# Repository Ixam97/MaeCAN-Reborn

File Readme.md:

# <b>MäCAN _Reborn_ </b>

Die zweite Generaton der MäCAN-Komponenten für den [Märklin CAN-Bus][candoku]

- <b>[MäCAN _Bootloader_][bootloader]</b><br>
    
- <b>[MäCAN _MP5x16_][mp5x16]</b><br>

- <b>[MäCAN _Dx32_][dx32]</b><br>

## Changelog

### [2022-03-26.1]
#### Hinzugefügt:
 - MP5x8+S: Kombination aus Signal- und Weichendecoder zum testen, kompatibel mit der MP5x16-Platine.
#### Änderungen:
 - MP5+D | Rückmeldefehler behoben, Einstellungen für die Schaltzeit und -verzögerung.
 - MP5x16 | Rückmeldefehler behoben.
 - Bootloader | Unterstützt nun 16-Bit Page-Addresse (Rückwärtskomatibel mit alten Updatern).
 - Bootloader | Nach einem fehlerhaften oder abgebrochenen Update wird der Programmspeicher gelöscht. Das Gerät verbleibt im Booloader, bis ein Update erfolgreich abgeschlossen wurde.
 - Allgemein | Der CAN-Ringpuffer blockiert nicht mehr, wenn er voll läuft.

### [2021-09-14.1]
#### Hinzugefügt:
- Allgemein | Source und Binarys für den maecan-updater für SRSEII und Windows.
- Bootloader | Unterstützung für NScale Grundmodule.
- MP5+D | Abwandlung des MP5x16 für die alternative Nutzung einiger Ports.
#### Änderungen:
- MP5x16 | Korrekte Abhandlung von Config-Kanal-Abfragen durch ein Userinterface.
- Bootloader | UID-Vergleich korrigiert.
### [2021-03-13.2]
#### Hinzugefügt:
- Allgemein | Fehlermeldung hinzugefügt, falls MCAN mit einem nicht unterstützten Controller verwendet wird.

### [2021-03-13.1]
#### Änderungen:
- Allgemein | Die Dokumentation in mcan.h wurde umfangreich erweitert.
- Allgemein | Die Berechnung des Hash wird durch mcan_init() übernommen. Die vorgefertigten send-Funktionen benötigen keine UID und keinen Hash mehr als Parameter. Dx32 und MP5x16 wurden entsprechend angepasst.
- Allgemein compareUID() ist jetzt Teil von MCAN.

### [2021-03-12.1]
#### Änderungen:
- Allgemein | MCAN beinhaltet nun mcp2515_basic und wurde aufgeräumt, um die Nutzung zu vereinfachen. Eine nutzung in Arduino-Sketches ist möglich.

#### Hinzugefügt:
- Dx32 | Version 1.0, Konfiguration und EEPROM-Nutzung wurde vollständig integriert. 
- Dx32 | Der DIP-Schalter stellt folgende Funktionen bereit: 1: Bootloader-Modus (noch nicht im Bootloader integriert), 2: New Line bei SLCAN zum Debugging, 3: Silent-Mode reagiert nicht auf Ping-Anfragen

### [2021-01-27.1]
#### Hinzugefügt:
- Allgemein | In mcp2515_basic ist nun SLCAN integriert. Ist das Symbol "SLCAN" definiert wird die serielle Schnittstelle als CAN-Interface genutzt. Standard sind 500000 Baud. Hierfür wurde die Interruptbehandlung in mcp2515_basic integriert. Nach `init_mcp2515()` kann mit `readCanFrame()` ausgewertet werden. SLCAN und der physische CAN werden gleichwertig behandelt. Im selben Zuge wurde für CAN-Frames ein Ring-Buffer implementiert. SLCAN ist auch im Bootloader verfügbar.

#### Änderungen:
- MP5x16 | Die Ansteuerung der Status-LED wurde an Dx32 angeglichen.

### [2021-01-25.1]
#### Hinzugefügt:
- Allgemein | Neue Funktion "sendStatus" in der mcan-Bibliothek zum senden von Statuskanalwerten.
- Dx32 | Konfigurationskanal-Werte können abgefragt werden.

### [2021-01-24.1]
#### Änderungen:
- Allgemein | Ein Fehler in der Übertragung von Konfigurationskanälen in der mcan.c wurde behoben.
- Dx32 | Basisfunktionalität wurde hergestellt (Belegterkennung mit Timeout und Gleisspannungserkennung).

### [2021-01-05.1]
#### Änderungen:
- Allgemein | Die Firmware aller Koponenten sowie des Bootloaders wurden in einer Atmel Studio-Solution zusammen geführt, um auf gemeinsame Dateien zugreifen zu können.
- Allgemein | Vereinheitlichung von Ordner- und Dateinamen ohne Umlaute.
- Allgemein | Nicht benötigte defines in mcan.h entfernt und für den ATmega1280 hinzugefügt.
- MP5x16 | Die Heartbeat-LED hat einen Fade-Effekt erhalten.
- Bootloader | Unterstützung für den Dx32 mit ATmega1280.
- Dx32 | Leitungsbenennung für zwei Rückmelde-LEDs an die Portbenennung angepasst.

#### Hinzugefügt:
- Dx32 | Erste Testsoftware mit einem Lauflicht und Helligkeitssteuerung für die Rückmelde-LEDs.

### [2020-12-26.2]
#### Änderungen:
- Bootloader + MP5x16 | Anpassung an die Compiler-Flags für die CPU-Frequenz, da Delays nicht richtig funktioniert haben.
- MP5x16 | Kleinere Änderungen, mit denen bisherige Compiler-Warnungen behandelt wurden.

### [2020-12-26.1]
#### Änderungen:
- Dx32 | Fehlerhafte Anbindung der externen Taktquelle für die USB-Schnittstelle korrigiert (Hardware V1.1).
- Bootloader | Makefile hinzugefügt, mit der der Bootloader Außerhalb von Atmel Studio für eines oder alle Boards kompilliert werden kann (Software V1.2).
- Bootloader | main.c durch maecan-bootloader.c ersetzt.

#### Hinzugefügt:
- Bootloader | Vorkompillierte Hex-Dateien für Busankoppler und MP5x16 hinzugefügt.

### [2020-12-22.1]
#### Änderungen:
- MP5x16 | Möglichkeit einer einstellbaren ID über den DIP-Schalter für eine einfachere Adressierung.

#### Hinzugefügt
- Dx32 | Erster Upload der Hardware.

### [2020-08-27.2]
#### Änderungen:
- Readme-Dateien angepasst

### [2020-08-27.1]
#### Hinzugefügt:
- MP5x16 | Erster Upload
- Bootloader |  Erster Upload

[candoku]: https://www.maerklin.de/fileadmin/media/service/software-updates/cs2CAN-Protokoll-2_0.pdf
[bootloader]: Bootloader
[mp5x16]: MäCAN_MP5x16
[dx32]: MäCAN_Dx32

[//]: # (Orange: #FE7D37, Blau: #007EC6)

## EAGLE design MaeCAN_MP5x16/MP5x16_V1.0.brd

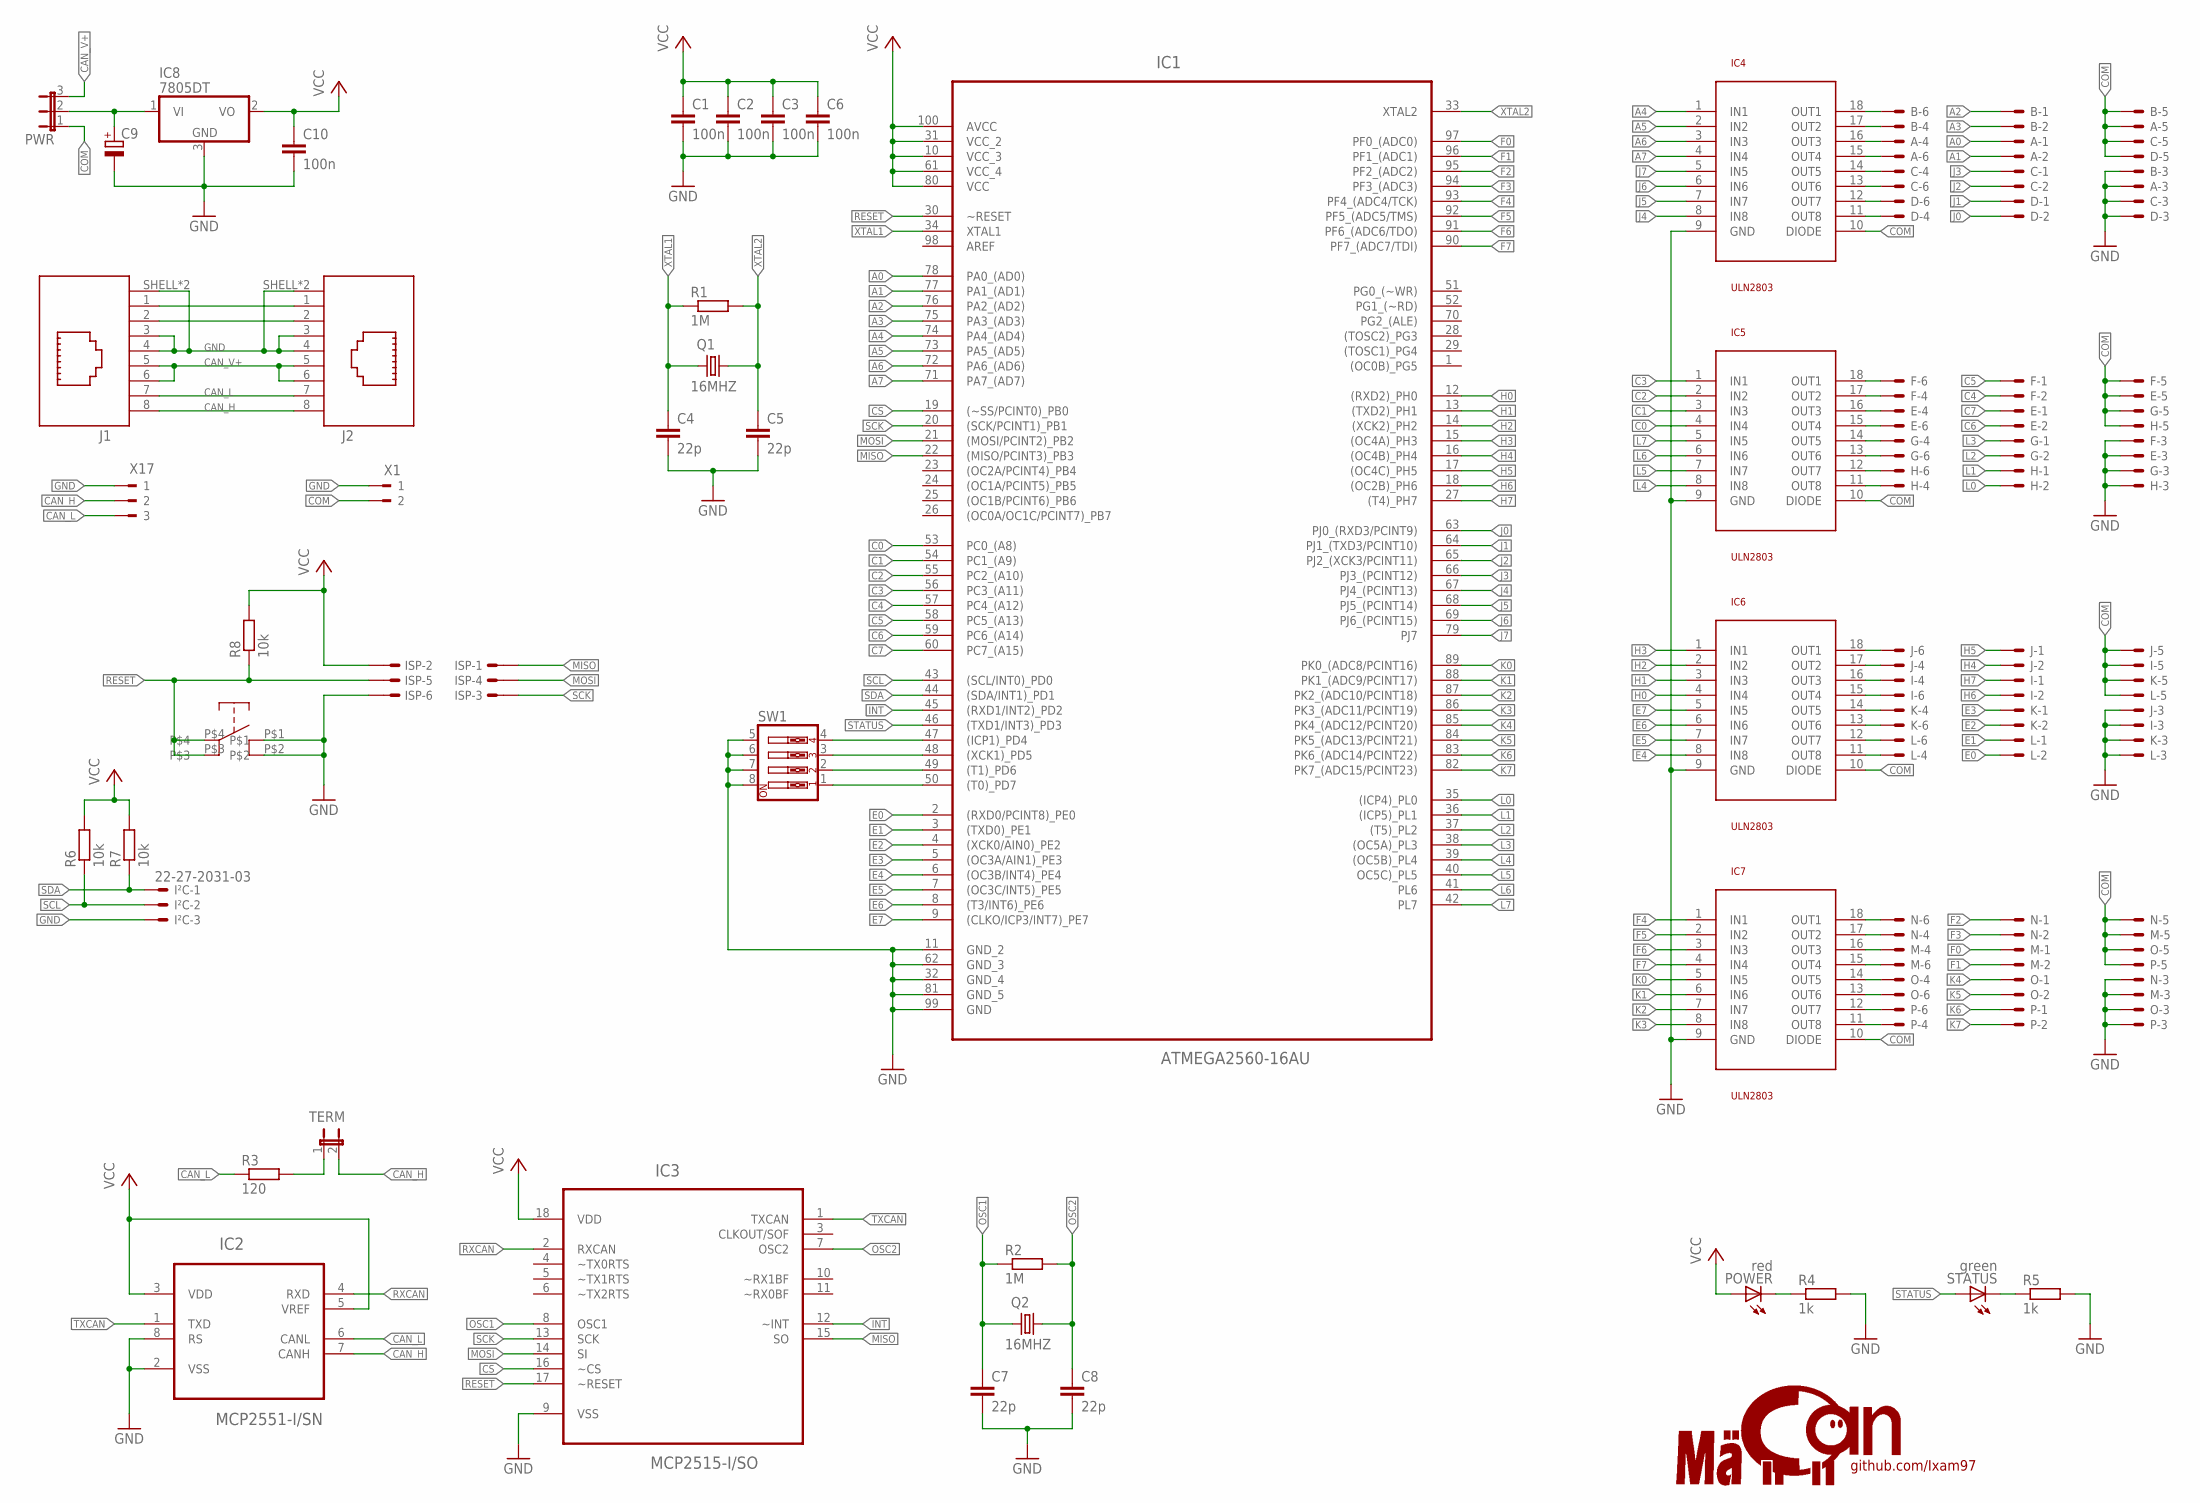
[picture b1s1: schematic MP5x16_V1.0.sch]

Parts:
A: 22-27-2061-06; 6410-06
B: 22-27-2061-06; 6410-06
C: 22-27-2061-06; 6410-06
C1, C2, C3, C6, C10: 100n; C0402
C4, C5, C7, C8: 22p; C0402
C9: CPOL-EUCT3216; CT3216
D: 22-27-2061-06; 6410-06
E: 22-27-2061-06; 6410-06
F: 22-27-2061-06; 6410-06
G: 22-27-2061-06; 6410-06
H: 22-27-2061-06; 6410-06
I: 22-27-2061-06; 6410-06
IC1: ATMEGA2560-16AU; QFP50P1600X1600X120-100N
IC2: MCP2551-I/SN; SOIC127P600X175-8N
IC3: MCP2515-I/SO; SOIC127P1034X264-18N
IC4, IC5, IC6, IC7: ULN2803; SO18L
IC8: 7805DT; TO252
ISP: 057-006-1
I²C: 22-27-2031-03; 6410-03
J: 22-27-2061-06; 6410-06
J1, J2: 615008140421
K: 22-27-2061-06; 6410-06
L: 22-27-2061-06; 6410-06
M: 22-27-2061-06; 6410-06
N: 22-27-2061-06; 6410-06
O: 22-27-2061-06; 6410-06
P: 22-27-2061-06; 6410-06
POWER: red; CHIP-LED0805
PWR: JP2E; JP2
Q1, Q2: 16MHZ; 3.2X2.5_KX-7
R1, R2: 1M; R0402
R3: 120; R0402
R4, R5: 1k; R0402
R6, R7, R8: 10k; R0402
STATUS: green; CHIP-LED0805
SW1: SW_DIP-4; EDG-04
TERM: JP1E; JP1
U$1: LOGO
U$15: BUTTON_JLC; BUTTON
X1: 180-2
X17: 180-3

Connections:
A0: A.1, IC1.78 (PA0_(AD0))
A1: A.2, IC1.77 (PA1_(AD1))
A2: B.1, IC1.76 (PA2_(AD2))
A3: B.2, IC1.75 (PA3_(AD3))
A4: IC1.74 (PA4_(AD4)), IC4.1 (IN1)
A5: IC1.73 (PA5_(AD5)), IC4.2 (IN2)
A6: IC1.72 (PA6_(AD6)), IC4.3 (IN3)
A7: IC1.71 (PA7_(AD7)), IC4.4 (IN4)
C0: IC1.53 (PC0_(A8)), IC5.4 (IN4)
C1: IC1.54 (PC1_(A9)), IC5.3 (IN3)
C2: IC1.55 (PC2_(A10)), IC5.2 (IN2)
C3: IC1.56 (PC3_(A11)), IC5.1 (IN1)
C4: F.2, IC1.57 (PC4_(A12))
C5: F.1, IC1.58 (PC5_(A13))
C6: E.2, IC1.59 (PC6_(A14))
C7: E.1, IC1.60 (PC7_(A15))
CAN_H: IC2.7 (CANH), J1.8, J2.8, TERM.2, X17.2
CAN_L: IC2.6 (CANL), J1.7, J2.7, R3.1, X17.3
CAN_V+: J1.5, J1.6, J2.5, J2.6, PWR.3
COM: A.5, B.5, C.5, D.5, E.5, F.5, G.5, H.5, I.5, IC4.10 (DIODE), IC5.10 (DIODE), IC6.10 (DIODE), IC7.10 (DIODE), J.5, K.5, L.5, M.5, N.5, O.5, P.5, PWR.1, X1.2
CS: IC1.19 ((~SS/PCINT0)_PB0), IC3.16 (~CS)
E0: IC1.2 ((RXD0/PCINT8)_PE0), L.2
E1: IC1.3 ((TXD0)_PE1), L.1
E2: IC1.4 ((XCK0/AIN0)_PE2), K.2
E3: IC1.5 ((OC3A/AIN1)_PE3), K.1
E4: IC1.6 ((OC3B/INT4)_PE4), IC6.8 (IN8)
E5: IC1.7 ((OC3C/INT5)_PE5), IC6.7 (IN7)
E6: IC1.8 ((T3/INT6)_PE6), IC6.6 (IN6)
E7: IC1.9 ((CLKO/ICP3/INT7)_PE7), IC6.5 (IN5)
F0: IC1.97 (PF0_(ADC0)), M.1
F1: IC1.96 (PF1_(ADC1)), M.2
F2: IC1.95 (PF2_(ADC2)), N.1
F3: IC1.94 (PF3_(ADC3)), N.2
F4: IC1.93 (PF4_(ADC4/TCK)), IC7.1 (IN1)
F5: IC1.92 (PF5_(ADC5/TMS)), IC7.2 (IN2)
F6: IC1.91 (PF6_(ADC6/TDO)), IC7.3 (IN3)
F7: IC1.90 (PF7_(ADC7/TDI)), IC7.4 (IN4)
GND: A.3, B.3, C.3, C1.2, C2.2, C3.2, C4.2, C5.2, C6.2, C7.2, C8.2, C9.-, C10.2, D.3, E.3, F.3, G.3, H.3, I.3, IC1.11 (GND_2), IC1.32 (GND_4), IC1.62 (GND_3), IC1.81 (GND_5), IC1.99 (GND), IC2.2 (VSS), IC2.8 (RS), IC3.9 (VSS), IC4.9 (GND), IC5.9 (GND), IC6.9 (GND), IC7.9 (GND), IC8.3 (GND), ISP.6, I²C.3, J.3, J1.3, J1.4, J1.SHELL (SHIELD), J1.SHELL1 (SHIELD), J2.3, J2.4, J2.SHELL (SHIELD), J2.SHELL1 (SHIELD), K.3, L.3, M.3, N.3, O.3, P.3, R4.2, R5.2, SW1.5, SW1.6, SW1.7, SW1.8, U$15.P$1, U$15.P$2, X1.1, X17.1
H0: IC1.12 ((RXD2)_PH0), IC6.4 (IN4)
H1: IC1.13 ((TXD2)_PH1), IC6.3 (IN3)
H2: IC1.14 ((XCK2)_PH2), IC6.2 (IN2)
H3: IC1.15 ((OC4A)_PH3), IC6.1 (IN1)
H4: IC1.16 ((OC4B)_PH4), J.2
H5: IC1.17 ((OC4C)_PH5), J.1
H6: I.2, IC1.18 ((OC2B)_PH6)
H7: I.1, IC1.27 ((T4)_PH7)
INT: IC1.45 ((RXD1/INT2)_PD2), IC3.12 (~INT)
J0: D.2, IC1.63 (PJ0_(RXD3/PCINT9))
J1: D.1, IC1.64 (PJ1_(TXD3/PCINT10))
J2: C.2, IC1.65 (PJ2_(XCK3/PCINT11))
J3: C.1, IC1.66 (PJ3_(PCINT12))
J4: IC1.67 (PJ4_(PCINT13)), IC4.8 (IN8)
J5: IC1.68 (PJ5_(PCINT14)), IC4.7 (IN7)
J6: IC1.69 (PJ6_(PCINT15)), IC4.6 (IN6)
J7: IC1.79 (PJ7), IC4.5 (IN5)
K0: IC1.89 (PK0_(ADC8/PCINT16)), IC7.5 (IN5)
K1: IC1.88 (PK1_(ADC9/PCINT17)), IC7.6 (IN6)
K2: IC1.87 (PK2_(ADC10/PCINT18)), IC7.7 (IN7)
K3: IC1.86 (PK3_(ADC11/PCINT19)), IC7.8 (IN8)
K4: IC1.85 (PK4_(ADC12/PCINT20)), O.1
K5: IC1.84 (PK5_(ADC13/PCINT21)), O.2
K6: IC1.83 (PK6_(ADC14/PCINT22)), P.1
K7: IC1.82 (PK7_(ADC15/PCINT23)), P.2
L0: H.2, IC1.35 ((ICP4)_PL0)
L1: H.1, IC1.36 ((ICP5)_PL1)
L2: G.2, IC1.37 ((T5)_PL2)
L3: G.1, IC1.38 ((OC5A)_PL3)
L4: IC1.39 ((OC5B)_PL4), IC5.8 (IN8)
L5: IC1.40 (OC5C)_PL5), IC5.7 (IN7)
L6: IC1.41 (PL6), IC5.6 (IN6)
L7: IC1.42 (PL7), IC5.5 (IN5)
MISO: IC1.22 ((MISO/PCINT3)_PB3), IC3.15 (SO), ISP.1
MOSI: IC1.21 ((MOSI/PCINT2)_PB2), IC3.14 (SI), ISP.4
unnamed: B.4, IC4.17 (OUT2)
unnamed: B.6, IC4.18 (OUT1)
unnamed: A.4, IC4.16 (OUT3)
unnamed: A.6, IC4.15 (OUT4)
unnamed: C.4, IC4.14 (OUT5)
unnamed: C.6, IC4.13 (OUT6)
unnamed: D.6, IC4.12 (OUT7)
unnamed: D.4, IC4.11 (OUT8)
unnamed: F.6, IC5.18 (OUT1)
unnamed: F.4, IC5.17 (OUT2)
unnamed: E.6, IC5.15 (OUT4)
unnamed: E.4, IC5.16 (OUT3)
unnamed: G.4, IC5.14 (OUT5)
unnamed: G.6, IC5.13 (OUT6)
unnamed: H.6, IC5.12 (OUT7)
unnamed: H.4, IC5.11 (OUT8)
unnamed: IC1.47 ((ICP1)_PD4), SW1.4
unnamed: IC1.48 ((XCK1)_PD5), SW1.3
unnamed: IC1.49 ((T1)_PD6), SW1.2
unnamed: IC1.50 ((T0)_PD7), SW1.1
unnamed: J1.1, J2.1
unnamed: IC6.12 (OUT7), L.6
unnamed: IC7.12 (OUT7), P.6
unnamed: IC6.11 (OUT8), L.4
unnamed: I.4, IC6.16 (OUT3)
unnamed: I.6, IC6.15 (OUT4)
unnamed: IC6.14 (OUT5), K.4
unnamed: IC6.13 (OUT6), K.6
unnamed: IC6.17 (OUT2), J.4
unnamed: IC6.18 (OUT1), J.6
unnamed: IC7.11 (OUT8), P.4
unnamed: IC7.17 (OUT2), N.4
unnamed: IC7.16 (OUT3), M.4
unnamed: IC7.15 (OUT4), M.6
unnamed: IC7.14 (OUT5), O.4
unnamed: IC7.13 (OUT6), O.6
unnamed: IC7.18 (OUT1), N.6
unnamed: J1.2, J2.2
unnamed: POWER.C, R4.1
unnamed: R3.2, TERM.1
unnamed: R5.1, STATUS.C
OSC1: C7.1, IC3.8 (OSC1), Q2.1, R2.1
OSC2: C8.1, IC3.7 (OSC2), Q2.3 (2), R2.2
RESET: IC1.30 (~RESET), IC3.17 (~RESET), ISP.5, R8.1, U$15.P$3, U$15.P$4
RXCAN: IC2.4 (RXD), IC3.2 (RXCAN)
SCK: IC1.20 ((SCK/PCINT1)_PB1), IC3.13 (SCK), ISP.3
SCL: IC1.43 ((SCL/INT0)_PD0), I²C.2, R6.1
SDA: IC1.44 ((SDA/INT1)_PD1), I²C.1, R7.1
STATUS: IC1.46 ((TXD1/INT3)_PD3), STATUS.A
TXCAN: IC2.1 (TXD), IC3.1 (TXCAN)
V+: C9.+, IC8.1 (VI), PWR.2
VCC: C1.1, C2.1, C3.1, C6.1, C10.1, IC1.10 (VCC_3), IC1.31 (VCC_2), IC1.61 (VCC_4), IC1.80 (VCC), IC1.100 (AVCC), IC2.3 (VDD), IC2.5 (VREF), IC3.18 (VDD), IC8.2 (VO), ISP.2, POWER.A, R6.2, R7.2, R8.2
XTAL1: C4.1, IC1.34 (XTAL1), Q1.1, R1.1
XTAL2: C5.1, IC1.33 (XTAL2), Q1.3 (2), R1.2

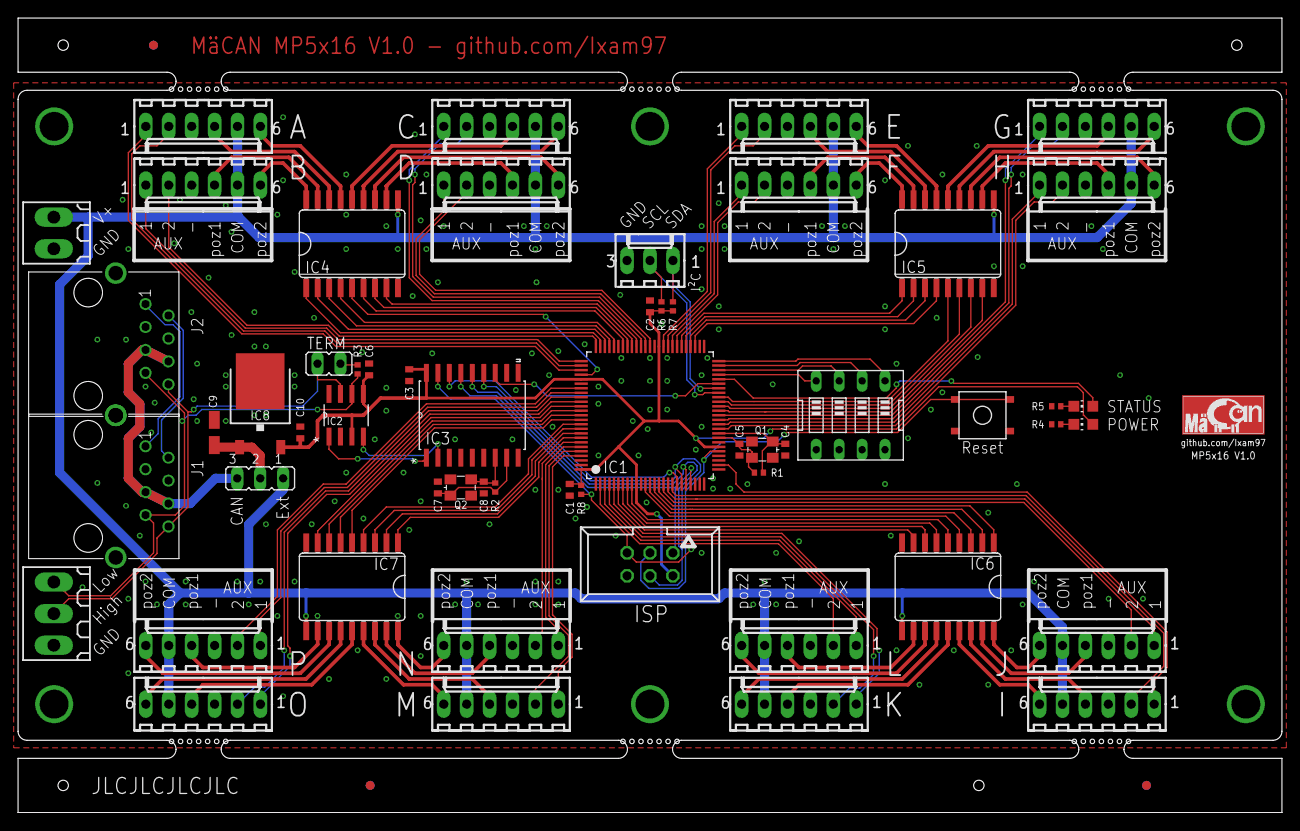
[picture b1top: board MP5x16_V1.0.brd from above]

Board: 2 copper layers, 140.0 x 88.0 mm, 70 parts (0 on the bottom side), 127 nets.

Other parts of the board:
U$2, U$3, U$4, U$5: JLCPCB_TOOLINGHOLE
U$6, U$7, U$8: FIDUCIAL
U$9, U$10, U$11, U$12, U$13, U$14: MOUSEBITESX7

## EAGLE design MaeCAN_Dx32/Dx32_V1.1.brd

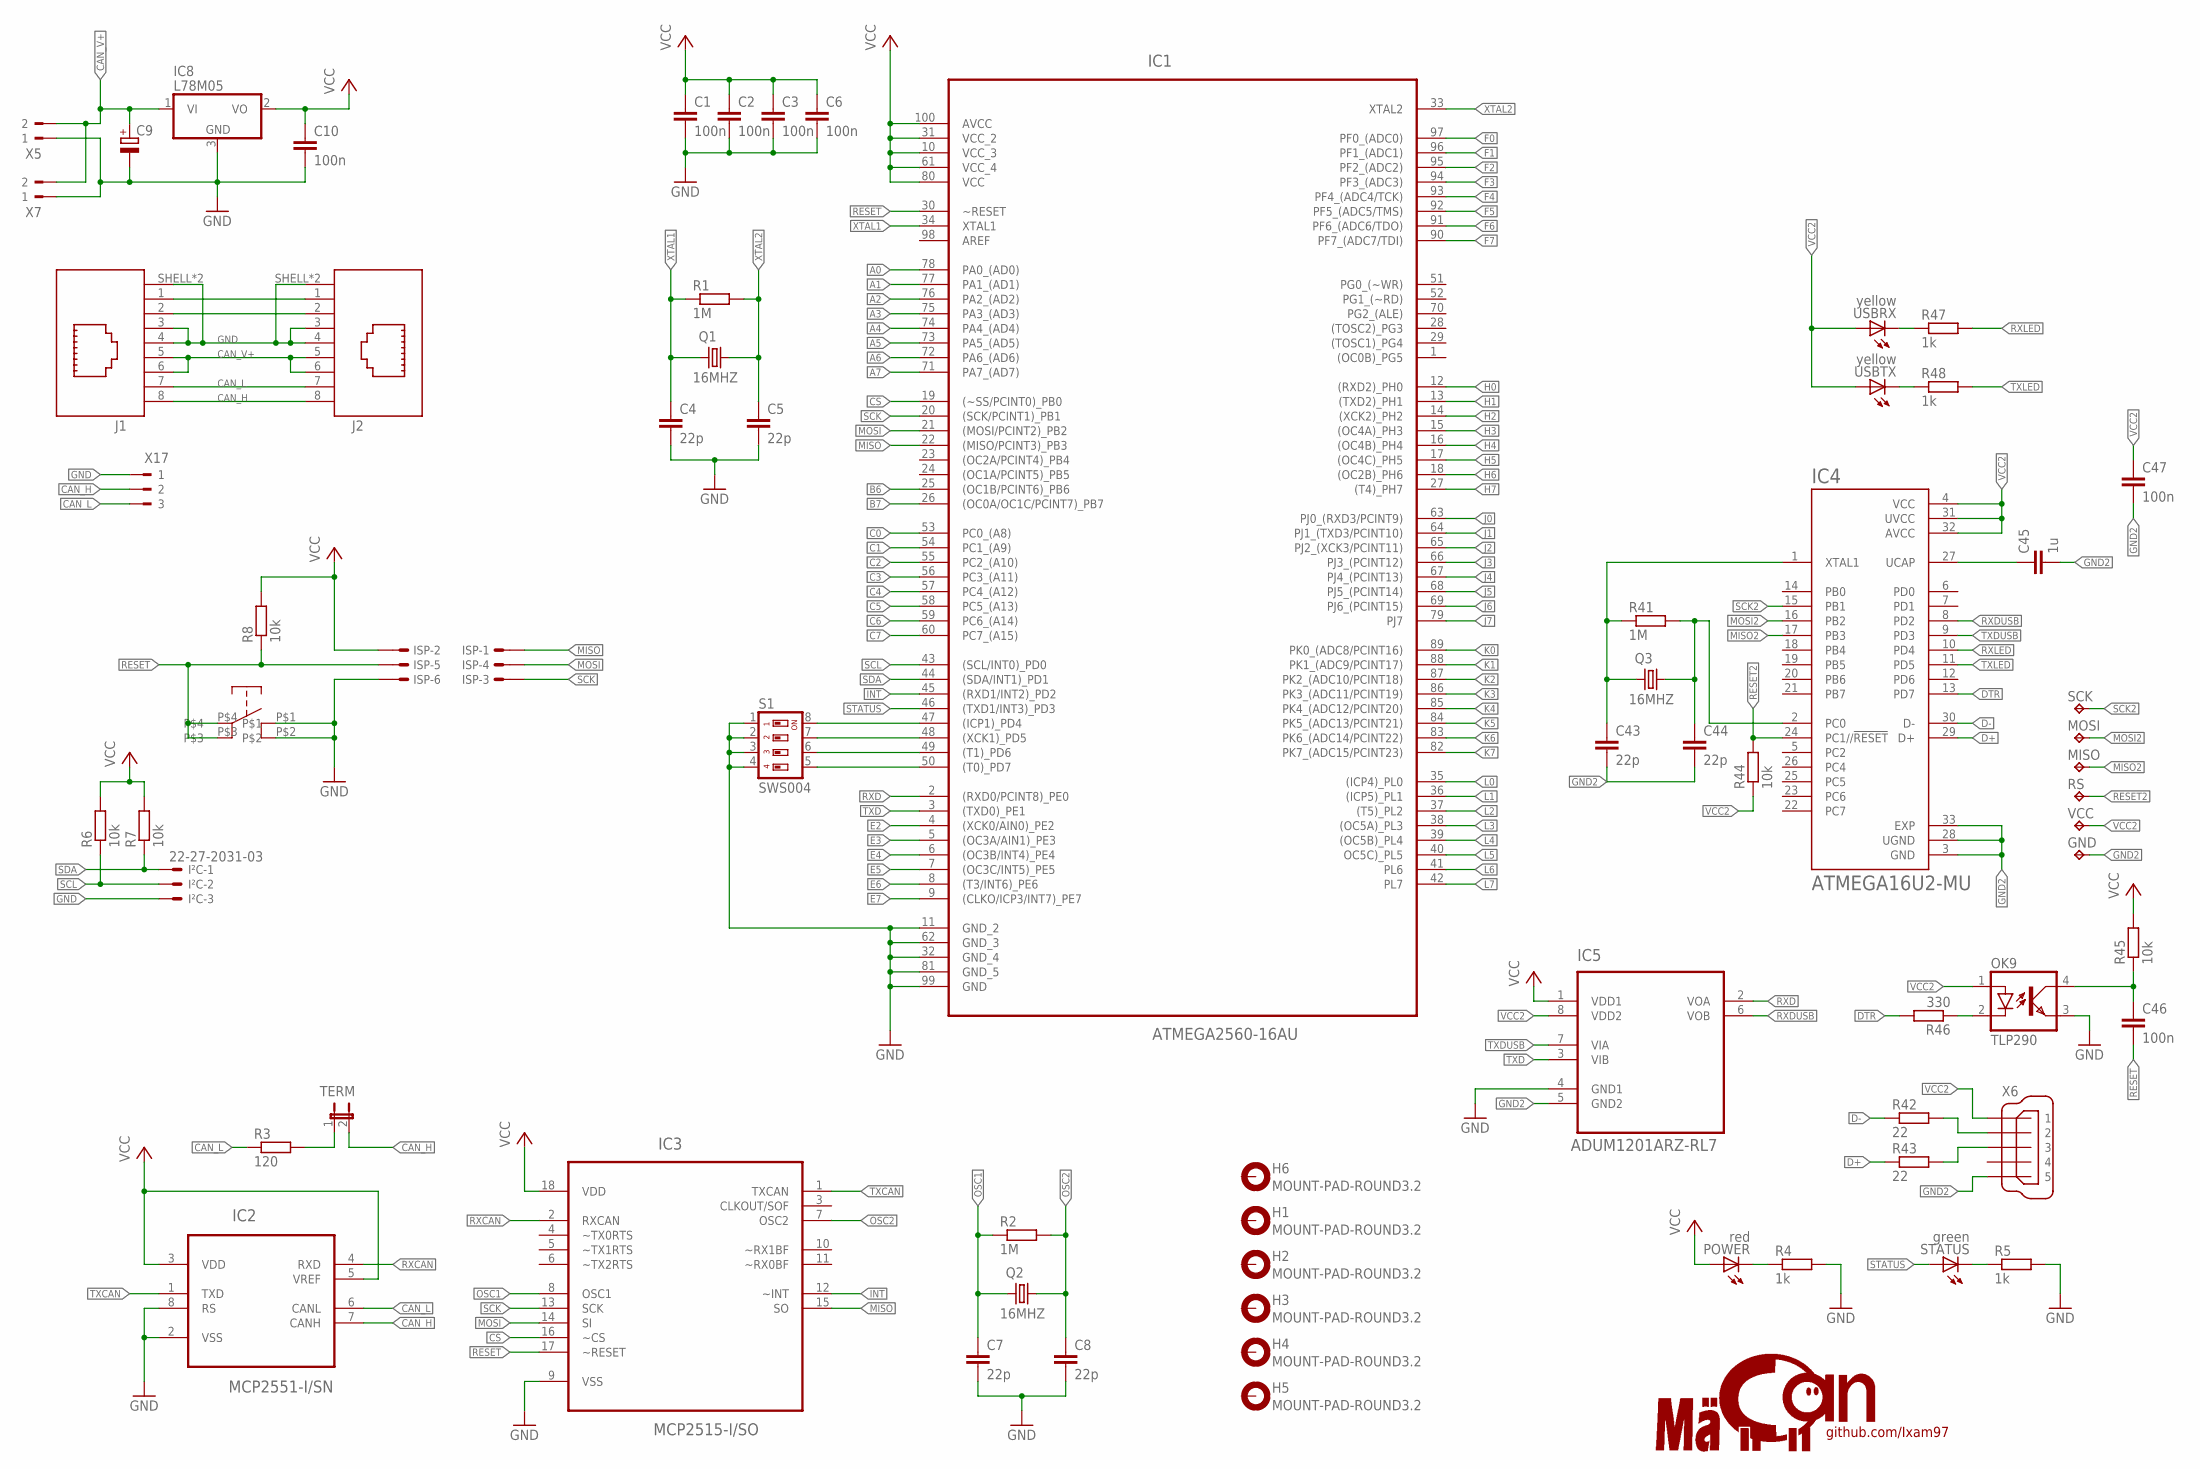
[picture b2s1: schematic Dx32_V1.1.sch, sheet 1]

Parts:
C1, C2, C3, C6, C10, C46, C47: 100n; C0402
C4, C5, C7, C8, C43, C44: 22p; C0402
C9: CPOL-EUCT3216; CT3216
C45: 1u; C0402
GND: TPB1,27; B1,27
H1, H2, H3, H4, H5, H6: MOUNT-PAD-ROUND3.2; 3,2-PAD
IC1: ATMEGA2560-16AU; QFP50P1600X1600X120-100N
IC2: MCP2551-I/SN; SOIC127P600X175-8N
IC3: MCP2515-I/SO; SOIC127P1034X264-18N
IC4: ATMEGA16U2-MU; QFN50P500X500X100-33N
IC5: ADUM1201ARZ-RL7; SOIC127P600X175-8N
IC8: L78M05; TO252; JLCPCB-PART C58069
ISP: 057-006-1
I²C: 22-27-2031-03; 6410-03
J1, J2: 615008140421
MISO: TPB1,27; B1,27
MOSI: TPB1,27; B1,27
OK9: TLP290; MINI-FLAT-4
POWER: red; CHIP-LED0805
Q1, Q2, Q3: 16MHZ; 3.2X2.5_KX-7
R1, R2, R41: 1M; R0402
R3: 120; R0402
R4, R5, R47, R48: 1k; R0402
R6, R7, R8, R44, R45: 10k; R0402
R42, R43: 22; R0402
R46: 330; R0402
RS: TPB1,27; B1,27
S1: SWS004; SMS-004
SCK: TPB1,27; B1,27
STATUS: green; CHIP-LED0805
TERM: JP1E; JP1
U$15: BUTTON_JLC; BUTTON
USBRX: yellow; CHIP-LED0805
USBTX: yellow; CHIP-LED0805
VCC: TPB1,27; B1,27
X5, X7: 180-2
X6: MINI-USB_SHIELD5P2-32005-601; 32005-601
X17: 180-3

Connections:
A0: IC1.78 (PA0_(AD0)); also elsewhere on the board
A1: IC1.77 (PA1_(AD1)); also elsewhere on the board
A2: IC1.76 (PA2_(AD2)); also elsewhere on the board
A3: IC1.75 (PA3_(AD3)); also elsewhere on the board
A4: IC1.74 (PA4_(AD4)); also elsewhere on the board
A5: IC1.73 (PA5_(AD5)); also elsewhere on the board
A6: IC1.72 (PA6_(AD6)); also elsewhere on the board
A7: IC1.71 (PA7_(AD7)); also elsewhere on the board
B6: IC1.25 ((OC1B/PCINT6)_PB6); also elsewhere on the board
B7: IC1.26 ((OC0A/OC1C/PCINT7)_PB7); also elsewhere on the board
C0: IC1.53 (PC0_(A8)); also elsewhere on the board
C1: IC1.54 (PC1_(A9)); also elsewhere on the board
C2: IC1.55 (PC2_(A10)); also elsewhere on the board
C3: IC1.56 (PC3_(A11)); also elsewhere on the board
C4: IC1.57 (PC4_(A12)); also elsewhere on the board
C5: IC1.58 (PC5_(A13)); also elsewhere on the board
C6: IC1.59 (PC6_(A14)); also elsewhere on the board
C7: IC1.60 (PC7_(A15)); also elsewhere on the board
CAN_H: IC2.7 (CANH), J1.8, J2.8, TERM.2, X17.2
CAN_L: IC2.6 (CANL), J1.7, J2.7, R3.1, X17.3
CAN_V+: C9.+, IC8.1 (VI), J1.5, J1.6, J2.5, J2.6, X5.2, X7.2
CS: IC1.19 ((~SS/PCINT0)_PB0), IC3.16 (~CS)
D+: IC4.29 (D+), R43.1
D-: IC4.30 (D-), R42.1
DTR: IC4.13 (PD7), R46.2
E2: IC1.4 ((XCK0/AIN0)_PE2); also elsewhere on the board
E3: IC1.5 ((OC3A/AIN1)_PE3); also elsewhere on the board
E4: IC1.6 ((OC3B/INT4)_PE4); also elsewhere on the board
E5: IC1.7 ((OC3C/INT5)_PE5); also elsewhere on the board
E6: IC1.8 ((T3/INT6)_PE6); also elsewhere on the board
E7: IC1.9 ((CLKO/ICP3/INT7)_PE7); also elsewhere on the board
F0: IC1.97 (PF0_(ADC0)); also elsewhere on the board
F1: IC1.96 (PF1_(ADC1)); also elsewhere on the board
F2: IC1.95 (PF2_(ADC2)); also elsewhere on the board
F3: IC1.94 (PF3_(ADC3)); also elsewhere on the board
F4: IC1.93 (PF4_(ADC4/TCK)); also elsewhere on the board
F5: IC1.92 (PF5_(ADC5/TMS)); also elsewhere on the board
F6: IC1.91 (PF6_(ADC6/TDO)); also elsewhere on the board
F7: IC1.90 (PF7_(ADC7/TDI)); also elsewhere on the board
GND: C1.2, C2.2, C3.2, C4.2, C5.2, C6.2, C7.2, C8.2, C9.-, C10.2, IC1.11 (GND_2), IC1.32 (GND_4), IC1.62 (GND_3), IC1.81 (GND_5), IC1.99 (GND), IC2.2 (VSS), IC2.8 (RS), IC3.9 (VSS), IC5.4 (GND1), IC8.3 (GND), ISP.6, I²C.3, J1.3, J1.4, J1.SHELL (SHIELD), J1.SHELL1 (SHIELD), J2.3, J2.4, J2.SHELL (SHIELD), J2.SHELL1 (SHIELD), OK9.3 (EMIT), R4.2, R5.2, S1.1, S1.2, S1.3, S1.4, U$15.P$1, U$15.P$2, X5.1, X7.1, X17.1; also elsewhere on the board
GND2: C43.2, C44.2, C45.2, C47.2, GND.TP, IC4.3 (GND), IC4.28 (UGND), IC4.33 (EXP), IC5.5 (GND2), X6.5
H0: IC1.12 ((RXD2)_PH0); also elsewhere on the board
H1: IC1.13 ((TXD2)_PH1); also elsewhere on the board
H2: IC1.14 ((XCK2)_PH2); also elsewhere on the board
H3: IC1.15 ((OC4A)_PH3); also elsewhere on the board
H4: IC1.16 ((OC4B)_PH4); also elsewhere on the board
H5: IC1.17 ((OC4C)_PH5); also elsewhere on the board
H6: IC1.18 ((OC2B)_PH6); also elsewhere on the board
H7: IC1.27 ((T4)_PH7); also elsewhere on the board
INT: IC1.45 ((RXD1/INT2)_PD2), IC3.12 (~INT)
J0: IC1.63 (PJ0_(RXD3/PCINT9)); also elsewhere on the board
J1: IC1.64 (PJ1_(TXD3/PCINT10)); also elsewhere on the board
J2: IC1.65 (PJ2_(XCK3/PCINT11)); also elsewhere on the board
J3: IC1.66 (PJ3_(PCINT12)); also elsewhere on the board
J4: IC1.67 (PJ4_(PCINT13)); also elsewhere on the board
J5: IC1.68 (PJ5_(PCINT14)); also elsewhere on the board
J6: IC1.69 (PJ6_(PCINT15)); also elsewhere on the board
J7: IC1.79 (PJ7); also elsewhere on the board
K0: IC1.89 (PK0_(ADC8/PCINT16)); also elsewhere on the board
K1: IC1.88 (PK1_(ADC9/PCINT17)); also elsewhere on the board
K2: IC1.87 (PK2_(ADC10/PCINT18)); also elsewhere on the board
K3: IC1.86 (PK3_(ADC11/PCINT19)); also elsewhere on the board
K4: IC1.85 (PK4_(ADC12/PCINT20)); also elsewhere on the board
K5: IC1.84 (PK5_(ADC13/PCINT21)); also elsewhere on the board
K6: IC1.83 (PK6_(ADC14/PCINT22)); also elsewhere on the board
K7: IC1.82 (PK7_(ADC15/PCINT23)); also elsewhere on the board
L0: IC1.35 ((ICP4)_PL0); also elsewhere on the board
L1: IC1.36 ((ICP5)_PL1); also elsewhere on the board
L2: IC1.37 ((T5)_PL2); also elsewhere on the board
L3: IC1.38 ((OC5A)_PL3); also elsewhere on the board
L4: IC1.39 ((OC5B)_PL4); also elsewhere on the board
L5: IC1.40 (OC5C)_PL5); also elsewhere on the board
L6: IC1.41 (PL6); also elsewhere on the board
L7: IC1.42 (PL7); also elsewhere on the board
MISO: IC1.22 ((MISO/PCINT3)_PB3), IC3.15 (SO), ISP.1
MISO2: IC4.17 (PB3), MISO.TP
MOSI: IC1.21 ((MOSI/PCINT2)_PB2), IC3.14 (SI), ISP.4
MOSI2: IC4.16 (PB2), MOSI.TP
unnamed: C46.1, OK9.4 (COL), R45.1
unnamed: IC1.47 ((ICP1)_PD4), S1.8
unnamed: IC1.48 ((XCK1)_PD5), S1.7
unnamed: IC1.49 ((T1)_PD6), S1.6
unnamed: IC1.50 ((T0)_PD7), S1.5
unnamed: J1.1, J2.1
unnamed: OK9.2 (C), R46.1
unnamed: J1.2, J2.2
unnamed: R48.1, USBTX.C
unnamed: R47.1, USBRX.C
unnamed: C45.1, IC4.27 (UCAP)
unnamed: R42.2, X6.2
unnamed: R43.2, X6.3
unnamed: POWER.C, R4.1
unnamed: R3.2, TERM.1
unnamed: R5.1, STATUS.C
OSC1: C7.1, IC3.8 (OSC1), Q2.1, R2.1
OSC2: C8.1, IC3.7 (OSC2), Q2.3 (2), R2.2
OSC3: C43.1, IC4.1 (XTAL1), Q3.1, R41.1
OSC4: C44.1, IC4.2 (PC0), Q3.3 (2), R41.2
RESET: C46.2, IC1.30 (~RESET), IC3.17 (~RESET), ISP.5, R8.1, U$15.P$3, U$15.P$4
RESET2: IC4.24 (PC1//!RESET), R44.2, RS.TP
RXCAN: IC2.4 (RXD), IC3.2 (RXCAN)
RXD: IC1.2 ((RXD0/PCINT8)_PE0), IC5.2 (VOA)
RXDUSB: IC4.8 (PD2), IC5.6 (VOB)
RXLED: IC4.10 (PD4), R47.2
SCK: IC1.20 ((SCK/PCINT1)_PB1), IC3.13 (SCK), ISP.3
SCK2: IC4.15 (PB1), SCK.TP
SCL: IC1.43 ((SCL/INT0)_PD0), I²C.2, R6.1
SDA: IC1.44 ((SDA/INT1)_PD1), I²C.1, R7.1
STATUS: IC1.46 ((TXD1/INT3)_PD3), STATUS.A
TXCAN: IC2.1 (TXD), IC3.1 (TXCAN)
TXD: IC1.3 ((TXD0)_PE1), IC5.3 (VIB)
TXDUSB: IC4.9 (PD3), IC5.7 (VIA)
TXLED: IC4.11 (PD5), R48.2
VCC: C1.1, C2.1, C3.1, C6.1, C10.1, IC1.10 (VCC_3), IC1.31 (VCC_2), IC1.61 (VCC_4), IC1.80 (VCC), IC1.100 (AVCC), IC2.3 (VDD), IC2.5 (VREF), IC3.18 (VDD), IC5.1 (VDD1), IC8.2 (VO), ISP.2, POWER.A, R6.2, R7.2, R8.2, R45.2; also elsewhere on the board
VCC2: C47.1, IC4.4 (VCC), IC4.31 (UVCC), IC4.32 (AVCC), IC5.8 (VDD2), OK9.1 (A), R44.1, USBRX.A, USBTX.A, VCC.TP, X6.1
XTAL1: C4.1, IC1.34 (XTAL1), Q1.1, R1.1
XTAL2: C5.1, IC1.33 (XTAL2), Q1.3 (2), R1.2

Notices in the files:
MaeCAN_Dx32/Dx32_V1.1.brd:
MäCAN Dx32 V1.1 - © 2020 github.com/Ixam97
parts and their libraries:
crystal-geyer_V1_0: Copyright: Geyer-Electronic
MaeCAN_logo: © 2020 github.com/Ixam97
InputOutputIO: Copyright: Würth Elektronik
